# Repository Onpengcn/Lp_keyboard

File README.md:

# Lp_keyboard
Lp_keyboard
hello

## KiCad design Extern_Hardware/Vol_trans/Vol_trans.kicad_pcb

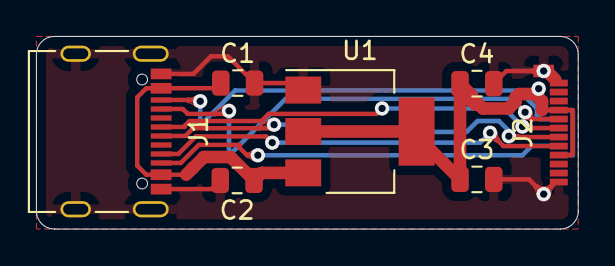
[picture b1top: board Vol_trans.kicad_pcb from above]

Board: 2 copper layers, 30.1 x 10.7 mm, 7 parts (0 on the bottom side), 9 nets.

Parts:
C1, C3: 10uf; C_0805_2012Metric
C2, C4: 0.1uf; C_0805_2012Metric
J1: USB_C_Receptacle_USB2.0; USB_C_Receptacle_Palconn_UTC16-G
J2: USB_C_Receptacle_USB2.0; USB_C_Plug_Molex_105444
U1: AMS1117-3.3; SOT-223-3_TabPin2

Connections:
3.3V: C3.1, C4.1, J2.A4, J2.A9, J2.B4, J2.B9, U1.2
5V: C1.1, C2.1, J1.A4, J1.A9, J1.B4, J1.B9, U1.3
GND: C1.2, C2.2, C3.2, C4.2, J1.A1, J1.A12, J1.B1, J1.B12, J1.S1, J2.A1, J2.A12, J2.B1, J2.B12, J2.S1, U1.1
unnamed: J1.A5, J2.A5
unnamed: J1.A6, J2.A6
unnamed: J1.A7, J2.A7
unnamed: J1.A8, J2.A8
unnamed: J1.B5, J2.B5
unnamed: J1.B8, J2.B8

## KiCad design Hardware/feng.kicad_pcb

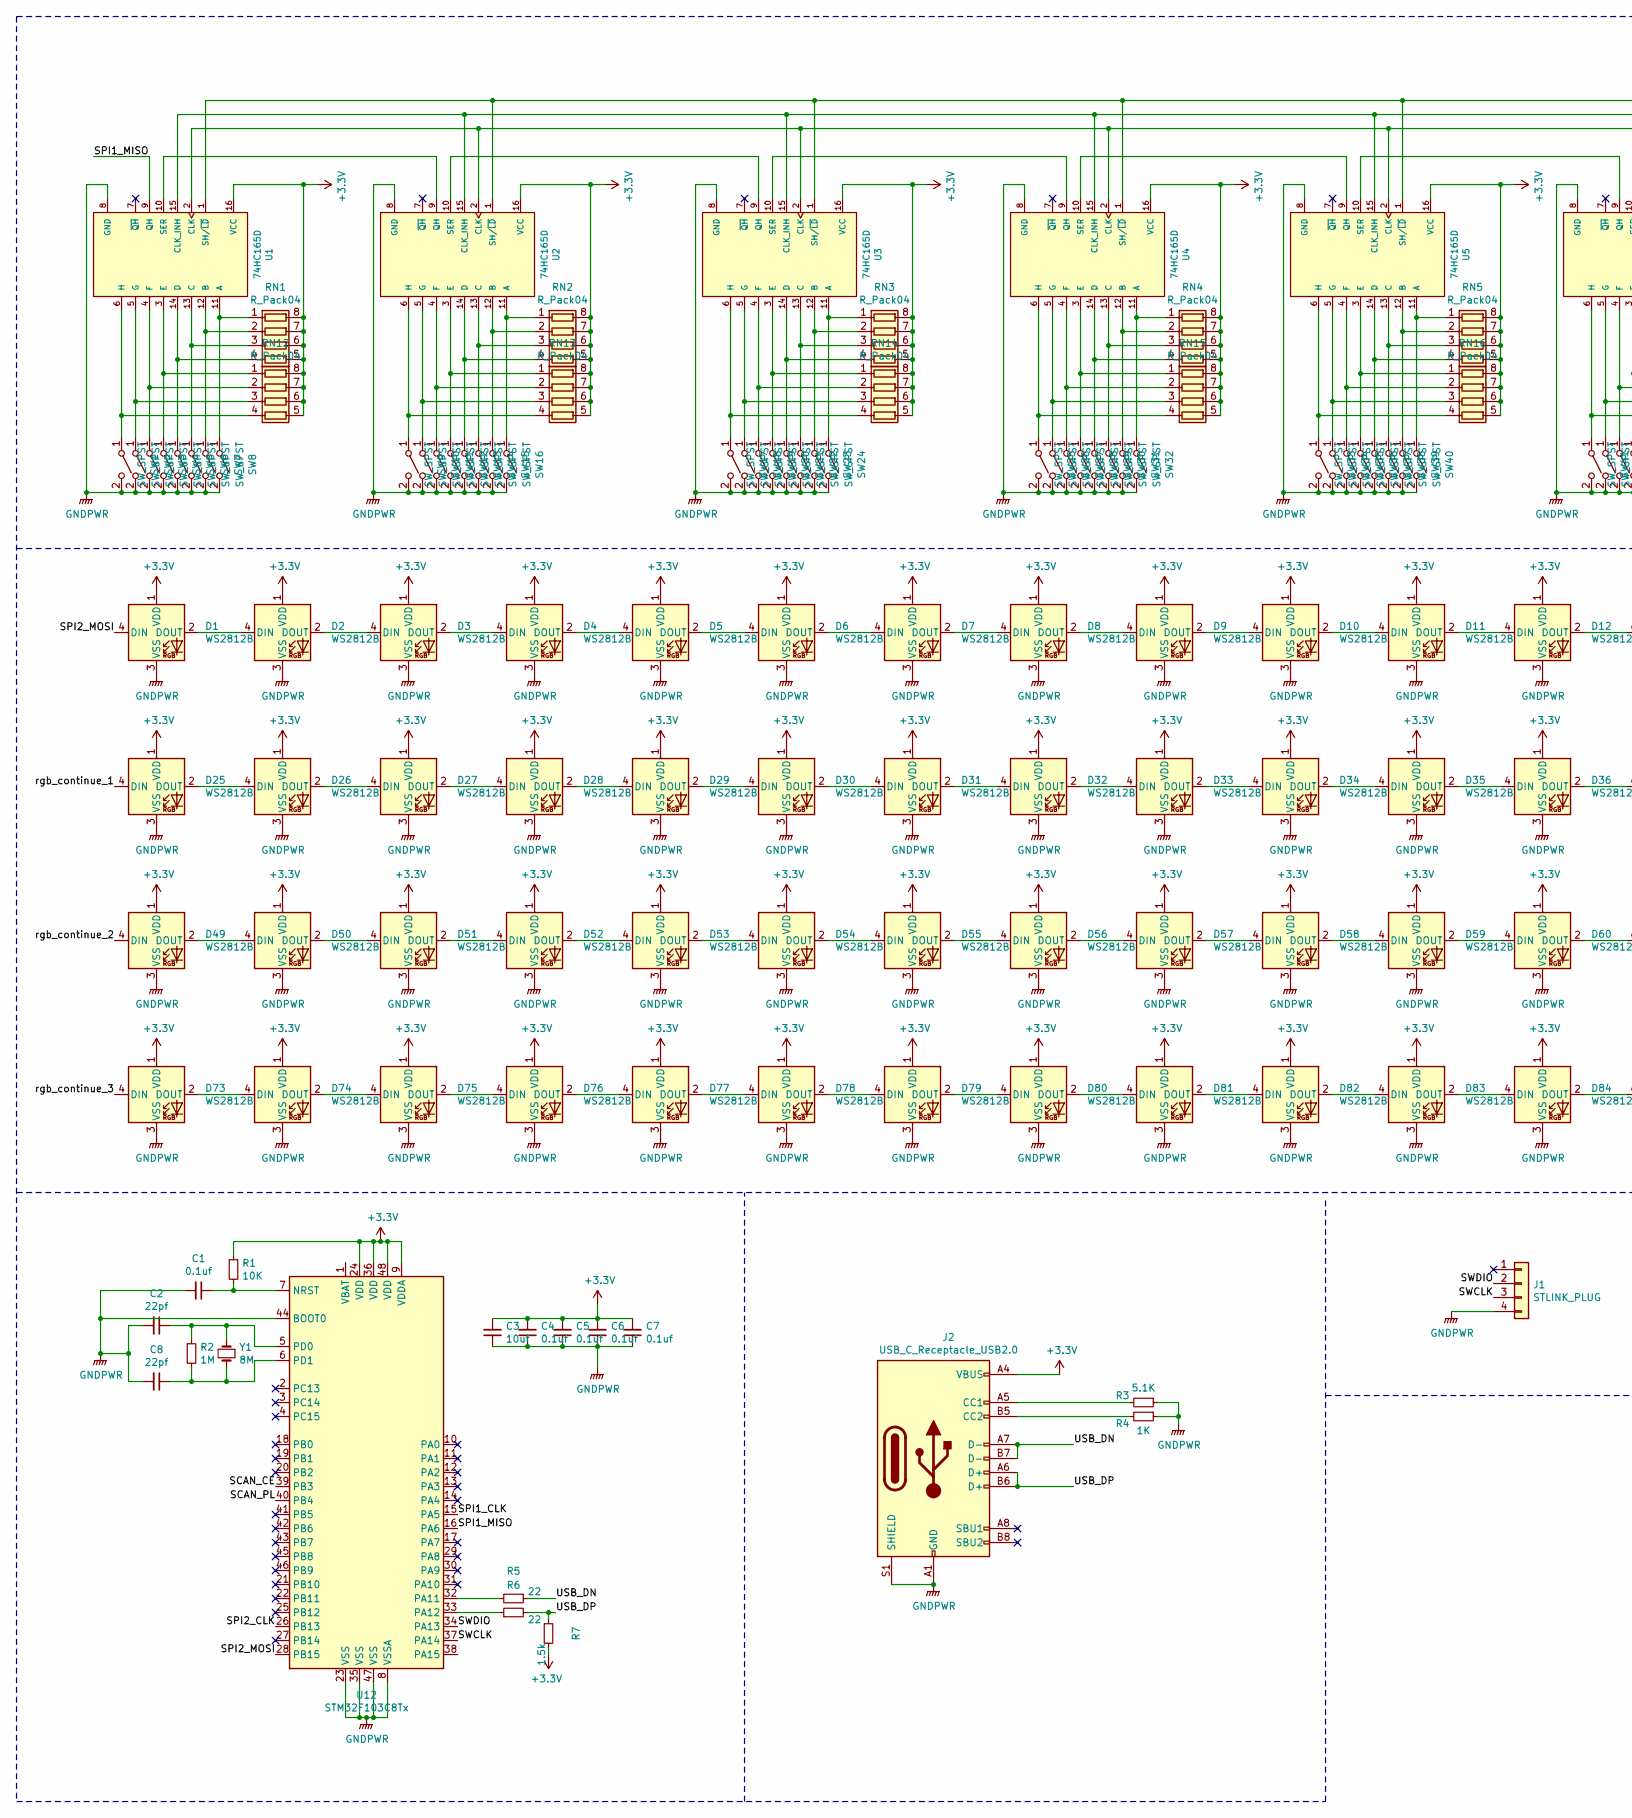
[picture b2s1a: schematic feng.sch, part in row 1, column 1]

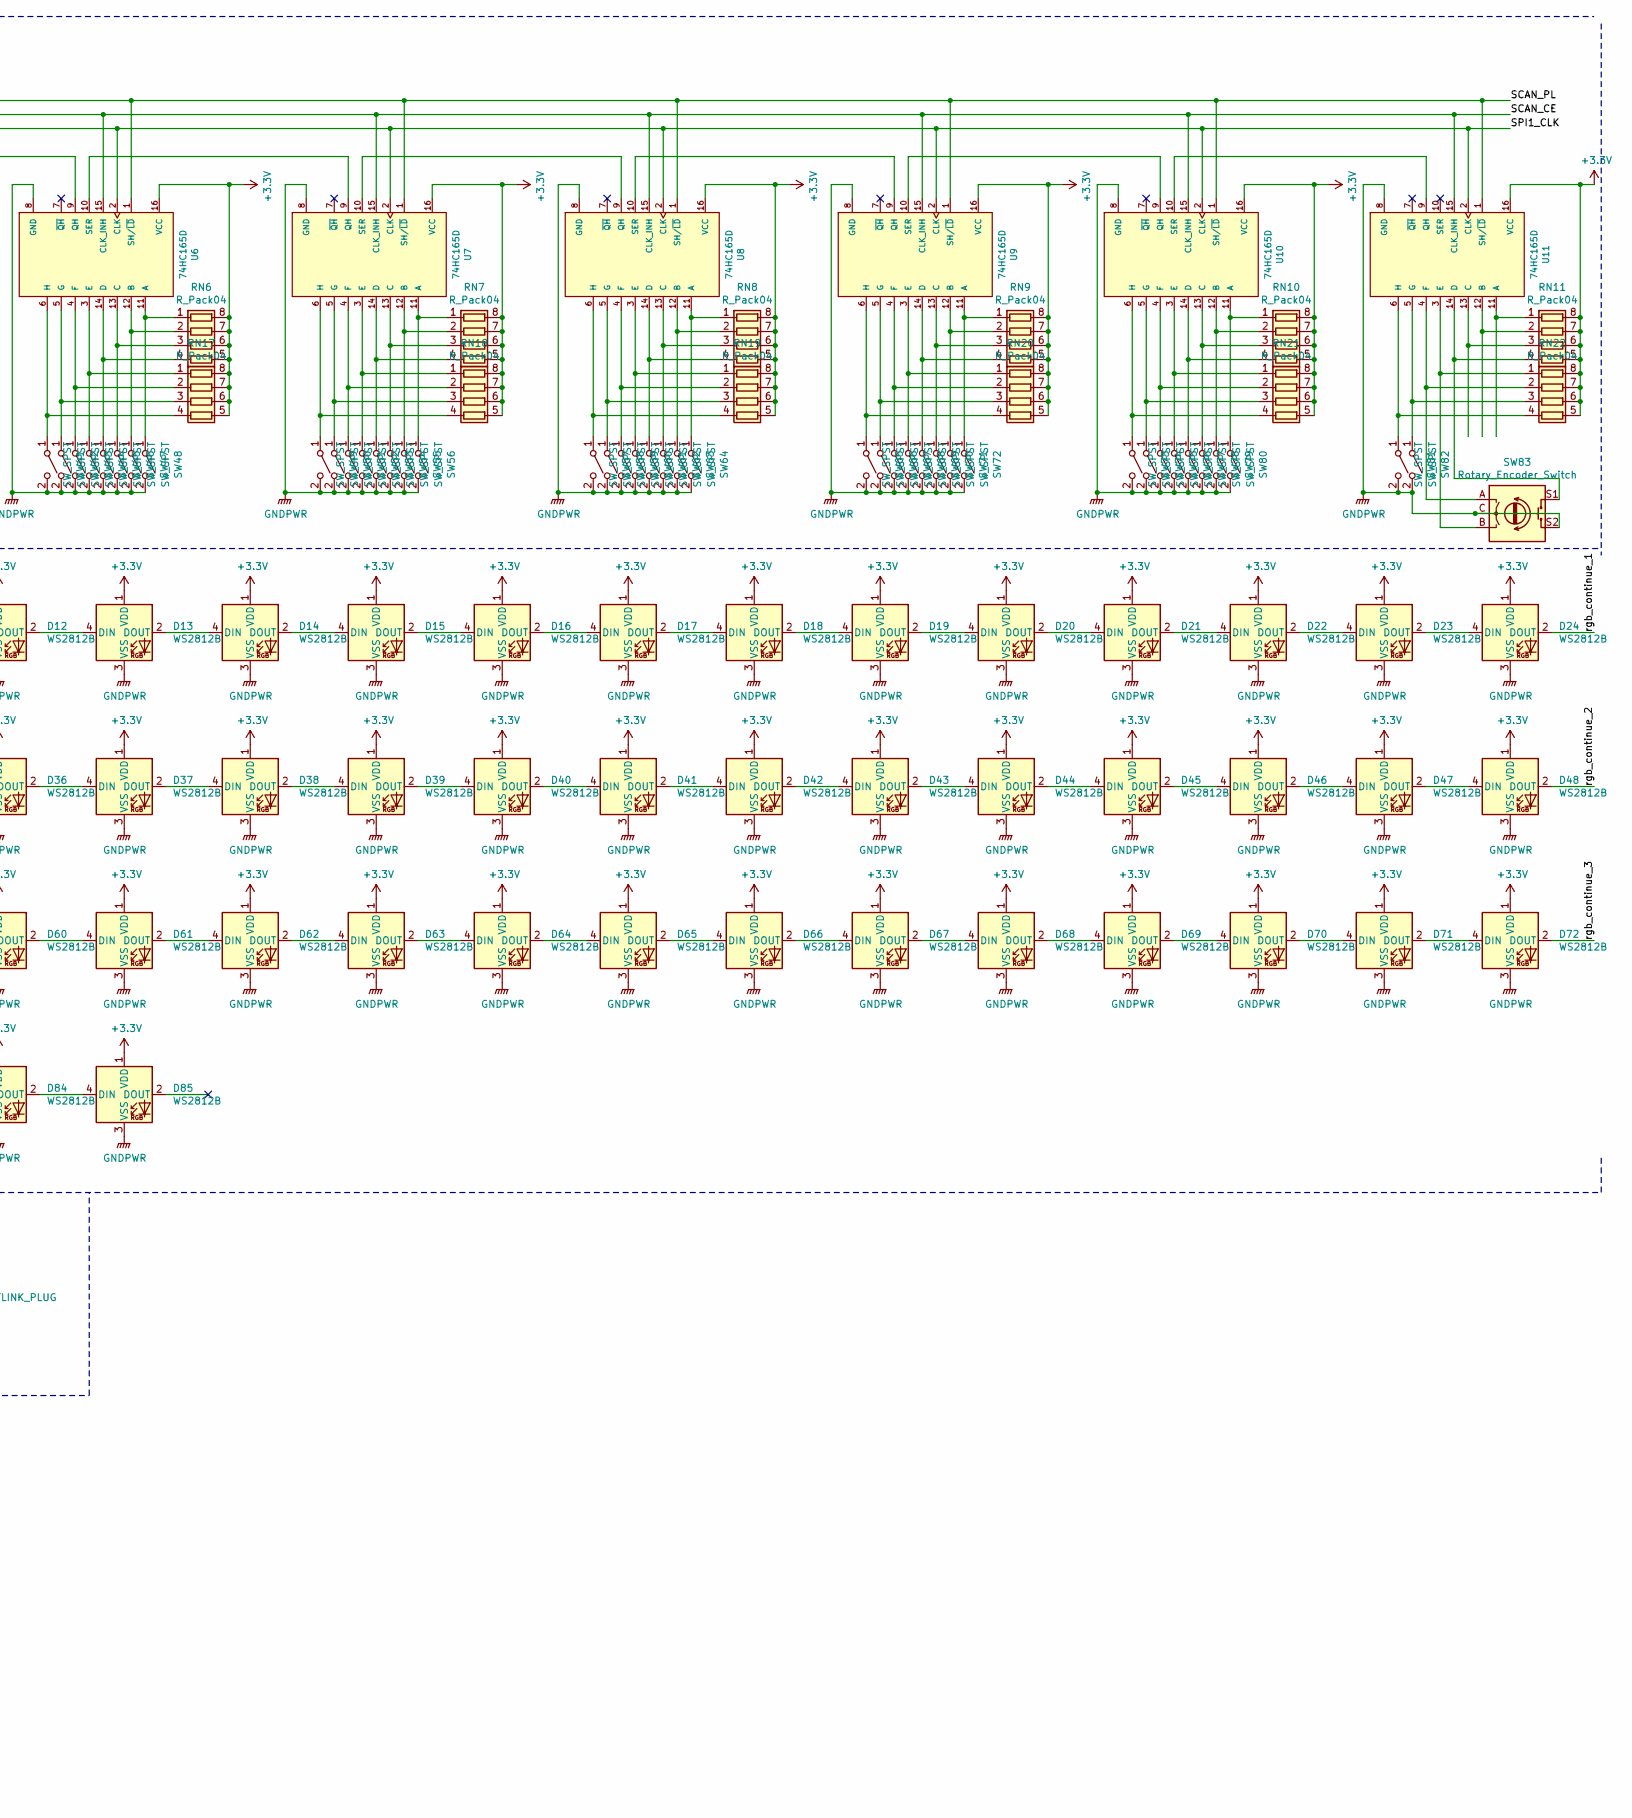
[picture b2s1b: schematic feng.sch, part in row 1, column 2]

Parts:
C1, C4, C5, C6, C7: 0.1uf; 0805
C2, C8: 22pf; 0805
C3: 10uf; 0805
D1, D2, D3, D4, D5, D6, D7, D8, D9, D10, D11, D12, D13, D14, D15, D16, D17, D18, D19, D20, D21, D22, D23, D24, D25, D26, D27, D28, D29, D30, D31, D32, D33, D34, D35, D36, D37, D38, D39, D40, D41, D42, D43, D44, D45, D46, D47, D48, D49, D50, D51, D52, D53, D54, D55, D56, D57, D58, D59, D60, D61, D62, D63, D64, D65, D66, D67, D68, D69, D70, D71, D72, D73, D74, D75, D76, D77, D78, D79, D80, D81, D82, D83, D84, D85: WS2812B; LED_WS2812B_PLCC4_5.0x5.0mm_P3.2mm
J1: STLINK_PLUG; PinHeader_1x04_P2.54mm_Vertical
J2: USB_C_Receptacle_USB2.0; USB_C_Receptacle_Palconn_UTC16-G
R1: 10K; 0805
R2: 1M; 0805
R3: 5.1K; 0805
R4: 1K; 0805
R5, R6: 22; 0805
R7: 1.5k; 0805
RN1, RN2, RN3, RN4, RN5, RN6, RN7, RN8, RN9, RN10, RN11, RN12, RN13, RN14, RN15, RN16, RN17, RN18, RN19, RN20, RN21, RN22: R_Pack04; R_Array_Convex_4x0603
SW1, SW2, SW3, SW4, SW5, SW6, SW7, SW8, SW9, SW10, SW11, SW12, SW13, SW14, SW15, SW16, SW17, SW18, SW19, SW20, SW21, SW22, SW23, SW24, SW25, SW26, SW27, SW28, SW29, SW30, SW31, SW32, SW33, SW34, SW35, SW36, SW37, SW38, SW39, SW40, SW41, SW42, SW43, SW44, SW45, SW46, SW47, SW48, SW49, SW50, SW51, SW52, SW53, SW54, SW55, SW56, SW57, SW58, SW59, SW60, SW61, SW62, SW63, SW64, SW65, SW66, SW67, SW68, SW69, SW70, SW71, SW72, SW73, SW74, SW75, SW76, SW77, SW78, SW79, SW80, SW81, SW82: SW_SPST; SW_Hotswap_Kailh_MX_1.00u
SW83: Rotary_Encoder_Switch; keyboard-RotaryEncoder_Alps_EC12E-Switch_Vertical_H20mm_Cir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
U1, U2, U3, U4, U5, U6, U7, U8, U9, U10, U11: 74HC165D; SOP-16_4.55x10.3mm_P1.27mm
U12: STM32F103C8Tx; LQFP-48_7x7mm_P0.5mm
Y1: 8M; Crystal_HC49-4H_Vertical

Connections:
+3V3: C3.2, C4.2, C5.2, C6.2, C7.2, D1.1 (VDD), D2.1 (VDD), D3.1 (VDD), D4.1 (VDD), D5.1 (VDD), D6.1 (VDD), D7.1 (VDD), D8.1 (VDD), D9.1 (VDD), D10.1 (VDD), D11.1 (VDD), D12.1 (VDD), D13.1 (VDD), D14.1 (VDD), D15.1 (VDD), D16.1 (VDD), D17.1 (VDD), D18.1 (VDD), D19.1 (VDD), D20.1 (VDD), D21.1 (VDD), D22.1 (VDD), D23.1 (VDD), D24.1 (VDD), D25.1 (VDD), D26.1 (VDD), D27.1 (VDD), D28.1 (VDD), D29.1 (VDD), D30.1 (VDD), D31.1 (VDD), D32.1 (VDD), D33.1 (VDD), D34.1 (VDD), D35.1 (VDD), D36.1 (VDD), D37.1 (VDD), D38.1 (VDD), D39.1 (VDD), D40.1 (VDD), D41.1 (VDD), D42.1 (VDD), D43.1 (VDD), D44.1 (VDD), D45.1 (VDD), D46.1 (VDD), D47.1 (VDD), D48.1 (VDD), D49.1 (VDD), D50.1 (VDD), D51.1 (VDD), D52.1 (VDD), D53.1 (VDD), D54.1 (VDD), D55.1 (VDD), D56.1 (VDD), D57.1 (VDD), D58.1 (VDD), D59.1 (VDD), D60.1 (VDD), D61.1 (VDD), D62.1 (VDD), D63.1 (VDD), D64.1 (VDD), D65.1 (VDD), D66.1 (VDD), D67.1 (VDD), D68.1 (VDD), D69.1 (VDD), D70.1 (VDD), D71.1 (VDD), D72.1 (VDD), D73.1 (VDD), D74.1 (VDD), D75.1 (VDD), D76.1 (VDD), D77.1 (VDD), D78.1 (VDD), D79.1 (VDD), D80.1 (VDD), D81.1 (VDD), D82.1 (VDD), D83.1 (VDD), D84.1 (VDD), D85.1 (VDD), J2.A4 (VBUS), J2.A9 (VBUS), J2.B4 (VBUS), J2.B9 (VBUS), R1.1, R7.2, RN1.5 (R4.2), RN1.6 (R3.2), RN1.7 (R2.2), RN1.8 (R1.2), RN2.5 (R4.2), RN2.6 (R3.2), RN2.7 (R2.2), RN2.8 (R1.2), RN3.5 (R4.2), RN3.6 (R3.2), RN3.7 (R2.2), RN3.8 (R1.2), RN4.5 (R4.2), RN4.6 (R3.2), RN4.7 (R2.2), RN4.8 (R1.2), RN5.5 (R4.2), RN5.6 (R3.2), RN5.7 (R2.2), RN5.8 (R1.2), RN6.5 (R4.2), RN6.6 (R3.2), RN6.7 (R2.2), RN6.8 (R1.2), RN7.5 (R4.2), RN7.6 (R3.2), RN7.7 (R2.2), RN7.8 (R1.2), RN8.5 (R4.2), RN8.6 (R3.2), RN8.7 (R2.2), RN8.8 (R1.2), RN9.5 (R4.2), RN9.6 (R3.2), RN9.7 (R2.2), RN9.8 (R1.2), RN10.5 (R4.2), RN10.6 (R3.2), RN10.7 (R2.2), RN10.8 (R1.2), RN11.5 (R4.2), RN11.6 (R3.2), RN11.7 (R2.2), RN11.8 (R1.2), RN12.5 (R4.2), RN12.6 (R3.2), RN12.7 (R2.2), RN12.8 (R1.2), RN13.5 (R4.2), RN13.6 (R3.2), RN13.7 (R2.2), RN13.8 (R1.2), RN14.5 (R4.2), RN14.6 (R3.2), RN14.7 (R2.2), RN14.8 (R1.2), RN15.5 (R4.2), RN15.6 (R3.2), RN15.7 (R2.2), RN15.8 (R1.2), RN16.5 (R4.2), RN16.6 (R3.2), RN16.7 (R2.2), RN16.8 (R1.2), RN17.5 (R4.2), RN17.6 (R3.2), RN17.7 (R2.2), RN17.8 (R1.2), RN18.5 (R4.2), RN18.6 (R3.2), RN18.7 (R2.2), RN18.8 (R1.2), RN19.5 (R4.2), RN19.6 (R3.2), RN19.7 (R2.2), RN19.8 (R1.2), RN20.5 (R4.2), RN20.6 (R3.2), RN20.7 (R2.2), RN20.8 (R1.2), RN21.5 (R4.2), RN21.6 (R3.2), RN21.7 (R2.2), RN21.8 (R1.2), RN22.5 (R4.2), RN22.6 (R3.2), RN22.7 (R2.2), RN22.8 (R1.2), U1.16 (VCC), U2.16 (VCC), U3.16 (VCC), U4.16 (VCC), U5.16 (VCC), U6.16 (VCC), U7.16 (VCC), U8.16 (VCC), U9.16 (VCC), U10.16 (VCC), U11.16 (VCC), U12.9 (VDDA), U12.24 (VDD), U12.36 (VDD), U12.48 (VDD)
/SCAN_CE: U1.15 (CLK_INH), U2.15 (CLK_INH), U3.15 (CLK_INH), U4.15 (CLK_INH), U5.15 (CLK_INH), U6.15 (CLK_INH), U7.15 (CLK_INH), U8.15 (CLK_INH), U9.15 (CLK_INH), U10.15 (CLK_INH), U11.15 (CLK_INH), U12.39 (PB3)
/SCAN_PL: U1.1 (SH/~LD), U2.1 (SH/~LD), U3.1 (SH/~LD), U4.1 (SH/~LD), U5.1 (SH/~LD), U6.1 (SH/~LD), U7.1 (SH/~LD), U8.1 (SH/~LD), U9.1 (SH/~LD), U10.1 (SH/~LD), U11.1 (SH/~LD), U12.40 (PB4)
/SPI1_CLK: U1.2 (CLK), U2.2 (CLK), U3.2 (CLK), U4.2 (CLK), U5.2 (CLK), U6.2 (CLK), U7.2 (CLK), U8.2 (CLK), U9.2 (CLK), U10.2 (CLK), U11.2 (CLK), U12.15 (PA5)
/SPI1_MISO: U1.9 (QH), U12.16 (PA6)
/SPI2_CLK: U12.26 (PB13)
/SPI2_MOSI: D1.4 (DIN), U12.28 (PB15)
/SWCLK: J1.3, U12.37 (PA14)
/SWDIO: J1.2, U12.34 (PA13)
/USB_DN: J2.A7 (D-), J2.B7 (D-), R5.1
/USB_DP: J2.A6 (D+), J2.B6 (D+), R6.2, R7.1
/rgb_continue_1: D24.2 (DOUT), D25.4 (DIN)
/rgb_continue_2: D48.2 (DOUT), D49.4 (DIN)
/rgb_continue_3: D72.2 (DOUT), D73.4 (DIN)
GNDPWR: C1.2, C2.2, C3.1, C4.1, C5.1, C6.1, C7.1, C8.2, D1.3 (VSS), D2.3 (VSS), D3.3 (VSS), D4.3 (VSS), D5.3 (VSS), D6.3 (VSS), D7.3 (VSS), D8.3 (VSS), D9.3 (VSS), D10.3 (VSS), D11.3 (VSS), D12.3 (VSS), D13.3 (VSS), D14.3 (VSS), D15.3 (VSS), D16.3 (VSS), D17.3 (VSS), D18.3 (VSS), D19.3 (VSS), D20.3 (VSS), D21.3 (VSS), D22.3 (VSS), D23.3 (VSS), D24.3 (VSS), D25.3 (VSS), D26.3 (VSS), D27.3 (VSS), D28.3 (VSS), D29.3 (VSS), D30.3 (VSS), D31.3 (VSS), D32.3 (VSS), D33.3 (VSS), D34.3 (VSS), D35.3 (VSS), D36.3 (VSS), D37.3 (VSS), D38.3 (VSS), D39.3 (VSS), D40.3 (VSS), D41.3 (VSS), D42.3 (VSS), D43.3 (VSS), D44.3 (VSS), D45.3 (VSS), D46.3 (VSS), D47.3 (VSS), D48.3 (VSS), D49.3 (VSS), D50.3 (VSS), D51.3 (VSS), D52.3 (VSS), D53.3 (VSS), D54.3 (VSS), D55.3 (VSS), D56.3 (VSS), D57.3 (VSS), D58.3 (VSS), D59.3 (VSS), D60.3 (VSS), D61.3 (VSS), D62.3 (VSS), D63.3 (VSS), D64.3 (VSS), D65.3 (VSS), D66.3 (VSS), D67.3 (VSS), D68.3 (VSS), D69.3 (VSS), D70.3 (VSS), D71.3 (VSS), D72.3 (VSS), D73.3 (VSS), D74.3 (VSS), D75.3 (VSS), D76.3 (VSS), D77.3 (VSS), D78.3 (VSS), D79.3 (VSS), D80.3 (VSS), D81.3 (VSS), D82.3 (VSS), D83.3 (VSS), D84.3 (VSS), D85.3 (VSS), J1.4, J2.A1 (GND), J2.A12 (GND), J2.B1 (GND), J2.B12 (GND), J2.S1 (SHIELD), R3.1, R4.1, SW1.2 (B), SW2.2 (B), SW3.2 (B), SW4.2 (B), SW5.2 (B), SW6.2 (B), SW7.2 (B), SW8.2 (B), SW9.2 (B), SW10.2 (B), SW11.2 (B), SW12.2 (B), SW13.2 (B), SW14.2 (B), SW15.2 (B), SW16.2 (B), SW17.2 (B), SW18.2 (B), SW19.2 (B), SW20.2 (B), SW21.2 (B), SW22.2 (B), SW23.2 (B), SW24.2 (B), SW25.2 (B), SW26.2 (B), SW27.2 (B), SW28.2 (B), SW29.2 (B), SW30.2 (B), SW31.2 (B), SW32.2 (B), SW33.2 (B), SW34.2 (B), SW35.2 (B), SW36.2 (B), SW37.2 (B), SW38.2 (B), SW39.2 (B), SW40.2 (B), SW41.2 (B), SW42.2 (B), SW43.2 (B), SW44.2 (B), SW45.2 (B), SW46.2 (B), SW47.2 (B), SW48.2 (B), SW49.2 (B), SW50.2 (B), SW51.2 (B), SW52.2 (B), SW53.2 (B), SW54.2 (B), SW55.2 (B), SW56.2 (B), SW57.2 (B), SW58.2 (B), SW59.2 (B), SW60.2 (B), SW61.2 (B), SW62.2 (B), SW63.2 (B), SW64.2 (B), SW65.2 (B), SW66.2 (B), SW67.2 (B), SW68.2 (B), SW69.2 (B), SW70.2 (B), SW71.2 (B), SW72.2 (B), SW73.2 (B), SW74.2 (B), SW75.2 (B), SW76.2 (B), SW77.2 (B), SW78.2 (B), SW79.2 (B), SW80.2 (B), SW81.2 (B), SW82.2 (B), SW83.C, SW83.S2, U1.8 (GND), U2.8 (GND), U3.8 (GND), U4.8 (GND), U5.8 (GND), U6.8 (GND), U7.8 (GND), U8.8 (GND), U9.8 (GND), U10.8 (GND), U11.8 (GND), U12.8 (VSSA), U12.23 (VSS), U12.35 (VSS), U12.44 (BOOT0), U12.47 (VSS)
unnamed: C1.1, R1.2, U12.7 (NRST)
unnamed: C2.1, R2.1, U12.5 (PD0), Y1.1
unnamed: C8.1, R2.2, U12.6 (PD1), Y1.2
unnamed: D1.2 (DOUT), D2.4 (DIN)
unnamed: D2.2 (DOUT), D3.4 (DIN)
unnamed: D3.2 (DOUT), D4.4 (DIN)
unnamed: D4.2 (DOUT), D5.4 (DIN)
unnamed: D5.2 (DOUT), D6.4 (DIN)
unnamed: D6.2 (DOUT), D7.4 (DIN)
unnamed: D7.2 (DOUT), D8.4 (DIN)
unnamed: D8.2 (DOUT), D9.4 (DIN)
unnamed: D10.2 (DOUT), D11.4 (DIN)
unnamed: D9.2 (DOUT), D10.4 (DIN)
unnamed: D11.2 (DOUT), D12.4 (DIN)
unnamed: D12.2 (DOUT), D13.4 (DIN)
unnamed: D13.2 (DOUT), D14.4 (DIN)
unnamed: D14.2 (DOUT), D15.4 (DIN)
unnamed: D15.2 (DOUT), D16.4 (DIN)
unnamed: D16.2 (DOUT), D17.4 (DIN)
unnamed: D17.2 (DOUT), D18.4 (DIN)
unnamed: D18.2 (DOUT), D19.4 (DIN)
unnamed: D19.2 (DOUT), D20.4 (DIN)
unnamed: D20.2 (DOUT), D21.4 (DIN)
unnamed: D21.2 (DOUT), D22.4 (DIN)
unnamed: D22.2 (DOUT), D23.4 (DIN)
unnamed: D23.2 (DOUT), D24.4 (DIN)
unnamed: D25.2 (DOUT), D26.4 (DIN)
unnamed: D26.2 (DOUT), D27.4 (DIN)
unnamed: D27.2 (DOUT), D28.4 (DIN)
unnamed: D28.2 (DOUT), D29.4 (DIN)
unnamed: D29.2 (DOUT), D30.4 (DIN)
unnamed: D30.2 (DOUT), D31.4 (DIN)
unnamed: D31.2 (DOUT), D32.4 (DIN)
unnamed: D32.2 (DOUT), D33.4 (DIN)
unnamed: D33.2 (DOUT), D34.4 (DIN)
unnamed: D34.2 (DOUT), D35.4 (DIN)
unnamed: D35.2 (DOUT), D36.4 (DIN)
unnamed: D36.2 (DOUT), D37.4 (DIN)
unnamed: D37.2 (DOUT), D38.4 (DIN)
unnamed: D38.2 (DOUT), D39.4 (DIN)
unnamed: D39.2 (DOUT), D40.4 (DIN)
unnamed: D40.2 (DOUT), D41.4 (DIN)
unnamed: D41.2 (DOUT), D42.4 (DIN)
unnamed: D42.2 (DOUT), D43.4 (DIN)
unnamed: D43.2 (DOUT), D44.4 (DIN)
unnamed: D44.2 (DOUT), D45.4 (DIN)
unnamed: D45.2 (DOUT), D46.4 (DIN)
unnamed: D46.2 (DOUT), D47.4 (DIN)
unnamed: D47.2 (DOUT), D48.4 (DIN)
unnamed: D49.2 (DOUT), D50.4 (DIN)
unnamed: D50.2 (DOUT), D51.4 (DIN)
unnamed: D51.2 (DOUT), D52.4 (DIN)
unnamed: D52.2 (DOUT), D53.4 (DIN)
unnamed: D53.2 (DOUT), D54.4 (DIN)
unnamed: D54.2 (DOUT), D55.4 (DIN)
unnamed: D55.2 (DOUT), D56.4 (DIN)
unnamed: D56.2 (DOUT), D57.4 (DIN)
unnamed: D57.2 (DOUT), D58.4 (DIN)
unnamed: D58.2 (DOUT), D59.4 (DIN)
unnamed: D59.2 (DOUT), D60.4 (DIN)
unnamed: D60.2 (DOUT), D61.4 (DIN)
unnamed: D61.2 (DOUT), D62.4 (DIN)
unnamed: D62.2 (DOUT), D63.4 (DIN)
unnamed: D63.2 (DOUT), D64.4 (DIN)
unnamed: D64.2 (DOUT), D65.4 (DIN)
unnamed: D65.2 (DOUT), D66.4 (DIN)
unnamed: D66.2 (DOUT), D67.4 (DIN)
unnamed: D67.2 (DOUT), D68.4 (DIN)
unnamed: D68.2 (DOUT), D69.4 (DIN)
unnamed: D69.2 (DOUT), D70.4 (DIN)
unnamed: D70.2 (DOUT), D71.4 (DIN)
unnamed: D71.2 (DOUT), D72.4 (DIN)
unnamed: D73.2 (DOUT), D74.4 (DIN)
unnamed: D74.2 (DOUT), D75.4 (DIN)
unnamed: D75.2 (DOUT), D76.4 (DIN)
unnamed: D76.2 (DOUT), D77.4 (DIN)
unnamed: D77.2 (DOUT), D78.4 (DIN)
unnamed: D78.2 (DOUT), D79.4 (DIN)
unnamed: D79.2 (DOUT), D80.4 (DIN)
unnamed: D80.2 (DOUT), D81.4 (DIN)
unnamed: D81.2 (DOUT), D82.4 (DIN)
unnamed: D82.2 (DOUT), D83.4 (DIN)
unnamed: D83.2 (DOUT), D84.4 (DIN)
unnamed: D84.2 (DOUT), D85.4 (DIN)
unnamed: J2.A5 (CC1), R3.2
unnamed: J2.B5 (CC2), R4.2
unnamed: R5.2, U12.32 (PA11)
unnamed: R6.1, U12.33 (PA12)
unnamed: RN1.1 (R1.1), SW8.1 (A), U1.11 (A)
unnamed: RN1.2 (R2.1), SW7.1 (A), U1.12 (B)
unnamed: RN1.3 (R3.1), SW6.1 (A), U1.13 (C)
unnamed: RN1.4 (R4.1), SW5.1 (A), U1.14 (D)
unnamed: RN2.1 (R1.1), SW16.1 (A), U2.11 (A)
unnamed: RN2.2 (R2.1), SW15.1 (A), U2.12 (B)
unnamed: RN2.3 (R3.1), SW14.1 (A), U2.13 (C)
unnamed: RN2.4 (R4.1), SW13.1 (A), U2.14 (D)
unnamed: RN3.1 (R1.1), SW24.1 (A), U3.11 (A)
unnamed: RN3.2 (R2.1), SW23.1 (A), U3.12 (B)
unnamed: RN3.3 (R3.1), SW22.1 (A), U3.13 (C)
unnamed: RN3.4 (R4.1), SW21.1 (A), U3.14 (D)
unnamed: RN4.1 (R1.1), SW32.1 (A), U4.11 (A)
unnamed: RN4.2 (R2.1), SW31.1 (A), U4.12 (B)
unnamed: RN4.3 (R3.1), SW30.1 (A), U4.13 (C)
unnamed: RN4.4 (R4.1), SW29.1 (A), U4.14 (D)
unnamed: RN5.1 (R1.1), SW40.1 (A), U5.11 (A)
unnamed: RN5.2 (R2.1), SW39.1 (A), U5.12 (B)
unnamed: RN5.3 (R3.1), SW38.1 (A), U5.13 (C)
unnamed: RN5.4 (R4.1), SW37.1 (A), U5.14 (D)
unnamed: RN6.1 (R1.1), SW48.1 (A), U6.11 (A)
unnamed: RN6.2 (R2.1), SW47.1 (A), U6.12 (B)
unnamed: RN6.3 (R3.1), SW46.1 (A), U6.13 (C)
unnamed: RN6.4 (R4.1), SW45.1 (A), U6.14 (D)
unnamed: RN7.1 (R1.1), SW56.1 (A), U7.11 (A)
unnamed: RN7.2 (R2.1), SW55.1 (A), U7.12 (B)
unnamed: RN7.3 (R3.1), SW54.1 (A), U7.13 (C)
unnamed: RN7.4 (R4.1), SW53.1 (A), U7.14 (D)
unnamed: RN8.1 (R1.1), SW64.1 (A), U8.11 (A)
unnamed: RN8.2 (R2.1), SW63.1 (A), U8.12 (B)
unnamed: RN8.3 (R3.1), SW62.1 (A), U8.13 (C)
unnamed: RN8.4 (R4.1), SW61.1 (A), U8.14 (D)
unnamed: RN9.1 (R1.1), SW72.1 (A), U9.11 (A)
unnamed: RN9.2 (R2.1), SW71.1 (A), U9.12 (B)
unnamed: RN9.3 (R3.1), SW70.1 (A), U9.13 (C)
unnamed: RN9.4 (R4.1), SW69.1 (A), U9.14 (D)
unnamed: RN10.1 (R1.1), SW80.1 (A), U10.11 (A)
unnamed: RN10.2 (R2.1), SW79.1 (A), U10.12 (B)
unnamed: RN10.3 (R3.1), SW78.1 (A), U10.13 (C)
unnamed: RN10.4 (R4.1), SW77.1 (A), U10.14 (D)
unnamed: RN11.1 (R1.1), U11.11 (A)
unnamed: RN11.2 (R2.1), U11.12 (B)
unnamed: RN11.3 (R3.1), U11.13 (C)
unnamed: RN11.4 (R4.1), SW83.S1, U11.14 (D)
unnamed: RN12.1 (R1.1), SW4.1 (A), U1.3 (E)
unnamed: RN12.2 (R2.1), SW3.1 (A), U1.4 (F)
unnamed: RN12.3 (R3.1), SW2.1 (A), U1.5 (G)
unnamed: RN12.4 (R4.1), SW1.1 (A), U1.6 (H)
unnamed: RN13.1 (R1.1), SW12.1 (A), U2.3 (E)
unnamed: RN13.2 (R2.1), SW11.1 (A), U2.4 (F)
unnamed: RN13.3 (R3.1), SW10.1 (A), U2.5 (G)
unnamed: RN13.4 (R4.1), SW9.1 (A), U2.6 (H)
unnamed: RN14.1 (R1.1), SW20.1 (A), U3.3 (E)
unnamed: RN14.2 (R2.1), SW19.1 (A), U3.4 (F)
unnamed: RN14.3 (R3.1), SW18.1 (A), U3.5 (G)
unnamed: RN14.4 (R4.1), SW17.1 (A), U3.6 (H)
unnamed: RN15.1 (R1.1), SW28.1 (A), U4.3 (E)
unnamed: RN15.2 (R2.1), SW27.1 (A), U4.4 (F)
unnamed: RN15.3 (R3.1), SW26.1 (A), U4.5 (G)
unnamed: RN15.4 (R4.1), SW25.1 (A), U4.6 (H)
unnamed: RN16.1 (R1.1), SW36.1 (A), U5.3 (E)
unnamed: RN16.2 (R2.1), SW35.1 (A), U5.4 (F)
unnamed: RN16.3 (R3.1), SW34.1 (A), U5.5 (G)
unnamed: RN16.4 (R4.1), SW33.1 (A), U5.6 (H)
unnamed: RN17.1 (R1.1), SW44.1 (A), U6.3 (E)
unnamed: RN17.2 (R2.1), SW43.1 (A), U6.4 (F)
unnamed: RN17.3 (R3.1), SW42.1 (A), U6.5 (G)
unnamed: RN17.4 (R4.1), SW41.1 (A), U6.6 (H)
unnamed: RN18.1 (R1.1), SW52.1 (A), U7.3 (E)
unnamed: RN18.2 (R2.1), SW51.1 (A), U7.4 (F)
unnamed: RN18.3 (R3.1), SW50.1 (A), U7.5 (G)
unnamed: RN18.4 (R4.1), SW49.1 (A), U7.6 (H)
unnamed: RN19.1 (R1.1), SW60.1 (A), U8.3 (E)
unnamed: RN19.2 (R2.1), SW59.1 (A), U8.4 (F)
unnamed: RN19.3 (R3.1), SW58.1 (A), U8.5 (G)
unnamed: RN19.4 (R4.1), SW57.1 (A), U8.6 (H)
unnamed: RN20.1 (R1.1), SW68.1 (A), U9.3 (E)
unnamed: RN20.2 (R2.1), SW67.1 (A), U9.4 (F)
unnamed: RN20.3 (R3.1), SW66.1 (A), U9.5 (G)
unnamed: RN20.4 (R4.1), SW65.1 (A), U9.6 (H)
unnamed: RN21.1 (R1.1), SW76.1 (A), U10.3 (E)
unnamed: RN21.2 (R2.1), SW75.1 (A), U10.4 (F)
unnamed: RN21.3 (R3.1), SW74.1 (A), U10.5 (G)
unnamed: RN21.4 (R4.1), SW73.1 (A), U10.6 (H)
unnamed: RN22.1 (R1.1), SW83.B, U11.3 (E)
unnamed: RN22.2 (R2.1), SW83.A, U11.4 (F)
unnamed: RN22.3 (R3.1), SW82.1 (A), U11.5 (G)
unnamed: RN22.4 (R4.1), SW81.1 (A), U11.6 (H)
unnamed: U1.10 (SER), U2.9 (QH)
unnamed: U2.10 (SER), U3.9 (QH)
unnamed: U3.10 (SER), U4.9 (QH)
unnamed: U4.10 (SER), U5.9 (QH)
unnamed: U5.10 (SER), U6.9 (QH)
unnamed: U6.10 (SER), U7.9 (QH)
unnamed: U7.10 (SER), U8.9 (QH)
unnamed: U8.10 (SER), U9.9 (QH)
unnamed: U9.10 (SER), U10.9 (QH)
unnamed: U10.10 (SER), U11.9 (QH)

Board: 2 copper layers, 220 parts (0 on the bottom side), 200 nets, no tracks yet.

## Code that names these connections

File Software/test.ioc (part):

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Mcu.Name=STM32F103C(8-B)Tx
Mcu.Package=LQFP48
Mcu.UserName=STM32F103CBTx
PA11.Mode=Device
PA11.Signal=USB_DM
PA12.Mode=Device
PA12.Signal=USB_DP
PA13.Mode=Serial_Wire
PA13.Signal=SYS_JTMS-SWDIO
PA14.Mode=Serial_Wire
PA14.Signal=SYS_JTCK-SWCLK
PA5.Mode=RX_Only_Simplex_Unidirect_Master
PA5.Signal=SPI1_SCK
PA6.Mode=RX_Only_Simplex_Unidirect_Master
PA6.Signal=SPI1_MISO
PB3.GPIOParameters=GPIO_Label
PB3.GPIO_Label=SCAN_CE
PB3.Signal=GPIO_Output
PB4.GPIOParameters=GPIO_Label
PB4.GPIO_Label=SCAN_PL
PB4.Signal=GPIO_Output
PC13-TAMPER-RTC.Signal=GPIO_Output
PD0-OSC_IN.Mode=HSE-External-Oscillator
PD0-OSC_IN.Signal=RCC_OSC_IN
PD1-OSC_OUT.Mode=HSE-External-Oscillator
PD1-OSC_OUT.Signal=RCC_OSC_OUT
RCC.SYSCLKFreq_VALUE=72000000
RCC.SYSCLKSource=RCC_SYSCLKSOURCE_PLLCLK
board=custom

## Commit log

2022-08-21 开发分支
2022-08-21 Revert "开发分支"
2022-08-21 note
2022-08-21 pcb_50%
2022-08-23 pcb done
2023-06-04 patch for c6 chip and change some code
2023-06-20 first version
